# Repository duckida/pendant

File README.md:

# Pendant!

This is my submission to Hack Club Pendant YSWS!

I designed a small board with a rotary encoder, 2 push-buttons, 2 RGB LEDs, an OLED screen and a XIAO ESP32! It can be used for games, internet tasks with web APIs, Home Assistant control and more!

For part details, see [the BOM](https://github.com/duckida/pendant/blob/main/bom.md). To learn about how I designed this, check out the [journal](https://github.com/duckida/pendant/blob/main/journal.md)!

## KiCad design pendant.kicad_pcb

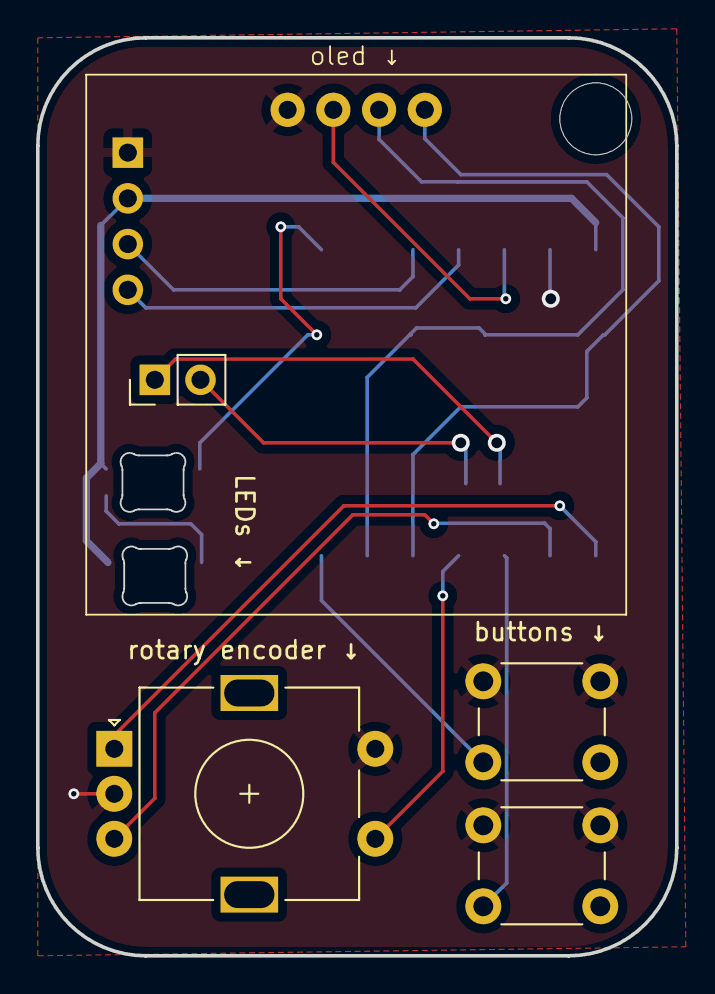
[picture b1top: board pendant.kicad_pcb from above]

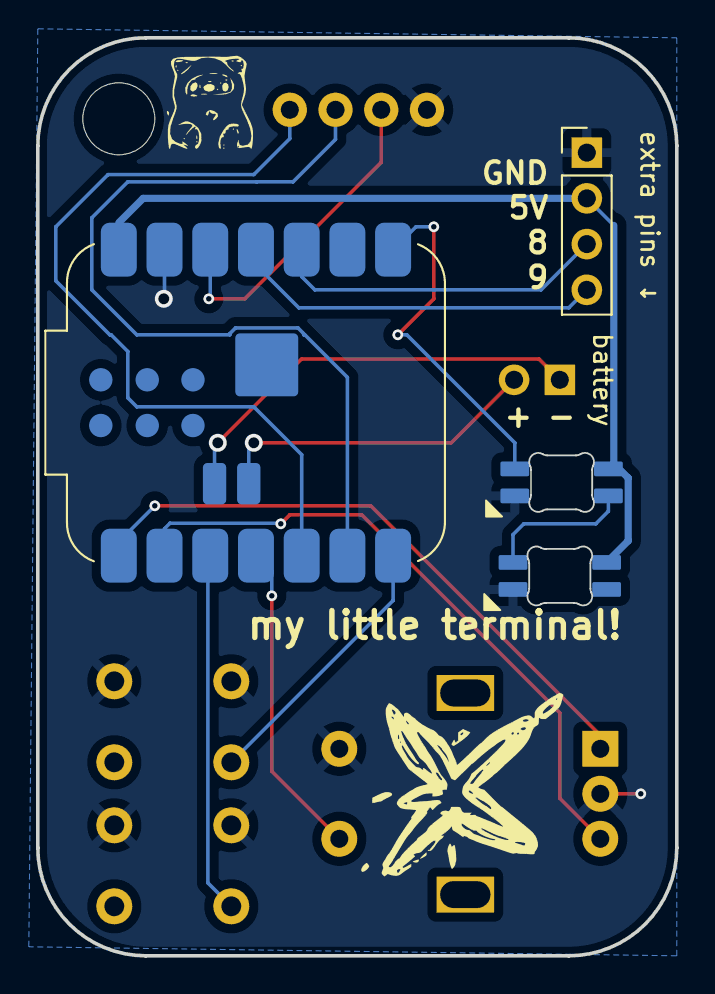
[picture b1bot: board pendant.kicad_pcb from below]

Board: 2 copper layers, 35.5 x 51.0 mm, 9 parts (2 on the bottom side), 16 nets.

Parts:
D1, D2: SK6812MINI; SK6812MINI-E_fixed
SW3: SW_Push; SW_PUSH_6mm_H4.3mm
U1: XIAO-ESP32-S3-DIP; MCU_Seeed_ESP32C3
battery: PinHeader_1x02_P2.54mm_Vertical
buttons ↓: SW_Push; SW_PUSH_6mm_H4.3mm
extra pins ↓: Extra Pins; PinHeader_1x04_P2.54mm_Vertical
oled ↓: SSD1306 OLED; SSD1306-OLED
rotary encoder ↓: RotaryEncoder_Switch; RotaryEncoder_Alps_EC11E-Switch_Vertical_H20mm

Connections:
+3V3: U1.12 (3V3), oled ↓.2
+5V: D1.1 (VDD), D2.1 (VDD), U1.14 (VBUS), extra pins ↓.2
/BTN2_GPIO: SW3.2, U1.3 (GPIO3_A2_D2)
/BTN_GPIO: U1.7 (GPIO43_D6_TX), buttons ↓.2
/EC_GPIO_A: U1.1 (GPIO1_A0_D0), rotary encoder ↓.A
/EC_GPIO_B: U1.2 (GPIO2_A1_D1), rotary encoder ↓.B
/EC_SW_GPIO: U1.4 (GPIO4_A3_D3), rotary encoder ↓.S1
/GPIO_8: U1.10 (GPIO8_A9_D9_MISO), extra pins ↓.3
/GPIO_9: U1.11 (GPIO9_A10_D10_MOSI), extra pins ↓.4
/LED_GPIO: D1.4 (DIN), U1.8 (GPIO44_D7_RX)
/SCL: U1.6 (GPIO6_A5_D5_SCL), oled ↓.2
/SDA: U1.5 (GPIO5_A4_D4_SDA), oled ↓.4
BAT+: U1.16, battery.2
BAT-: U1.17, battery.1
GND: D1.3 (VSS), D2.3 (VSS), SW3.1, U1.13 (GND), buttons ↓.1, extra pins ↓.1, oled ↓.1, rotary encoder ↓.C, rotary encoder ↓.S2
unnamed: D1.2 (DOUT), D2.4 (DIN)

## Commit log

2026-06-17 inital commit
2026-06-17 Add newlines to bom.md
2026-06-17 Initialize README with project details and images
    Added project description and images to README.
2026-06-17 Add battery connector
2026-06-17 Add battery polarity silkscreen
2026-06-17 Add 2-pin header for battery in journal
    Added a 2-pin header for battery connection with an image.
2026-06-18 Update BOM with detailed component descriptions
2026-06-18 Add SK6812 Mini E LEDs
2026-06-18 Document addition of LEDs to schematic and board
2026-06-18 Add LED details and images
2026-06-18 Convert to table with links
2026-06-18 Add Mouser links
2026-06-21 Add soup
2026-06-21 Add gitignore
